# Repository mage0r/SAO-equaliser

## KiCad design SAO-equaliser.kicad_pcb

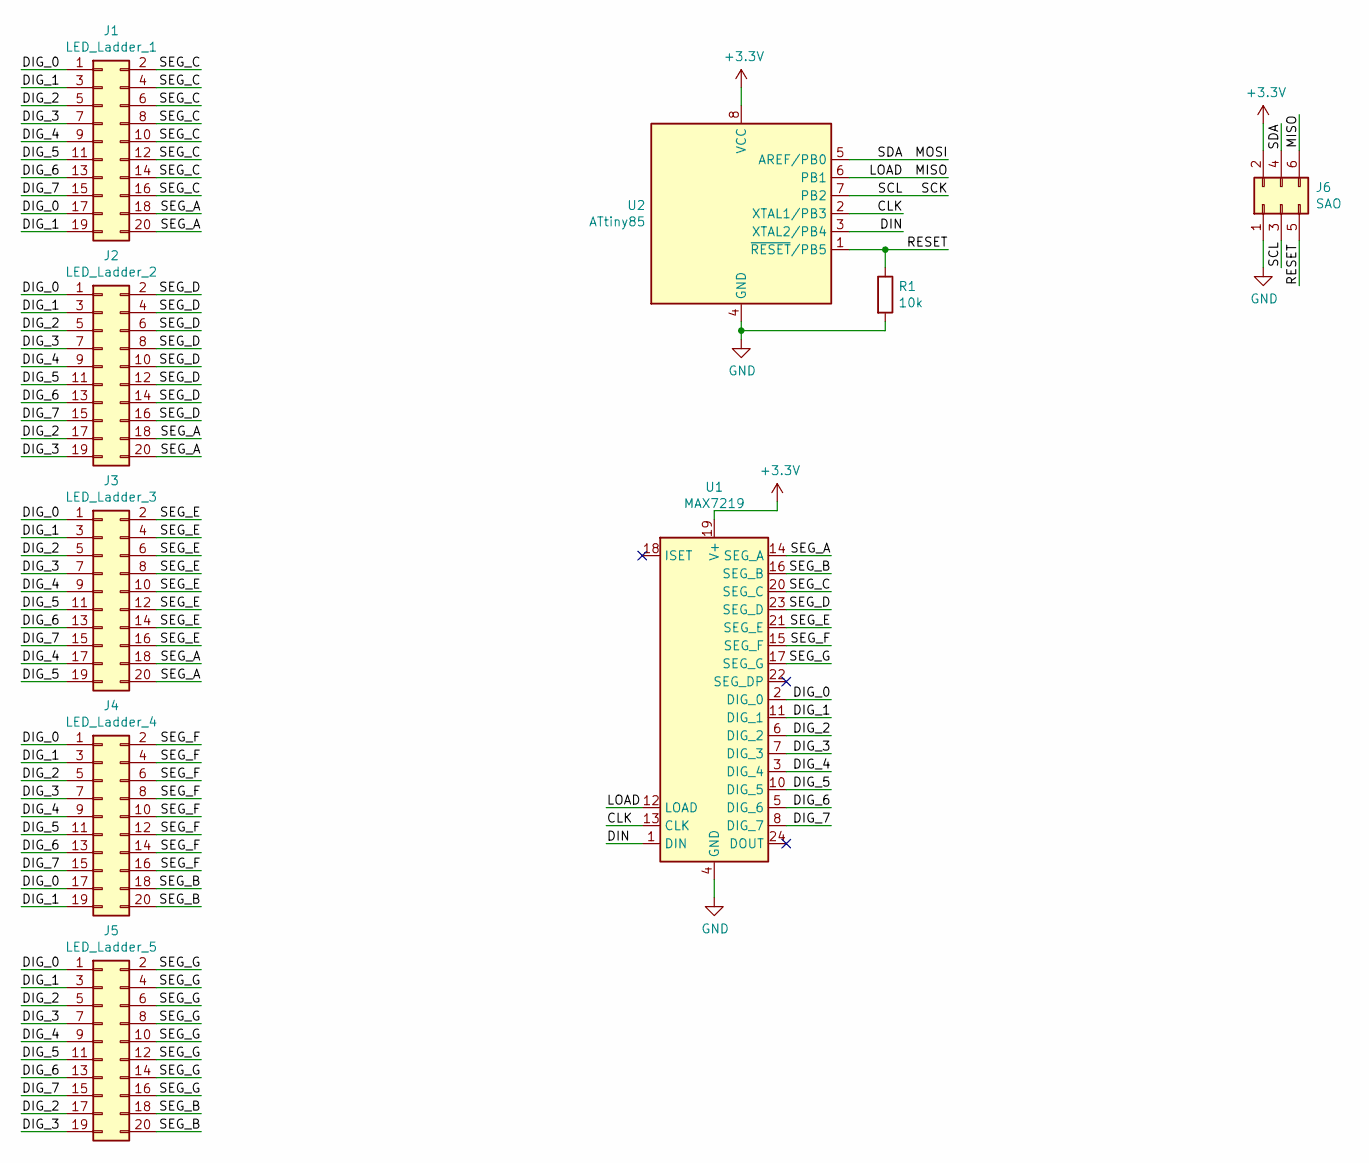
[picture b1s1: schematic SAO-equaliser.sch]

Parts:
J1: LED_Ladder_1; LED_array
J2: LED_Ladder_2; LED_array
J3: LED_Ladder_3; LED_array
J4: LED_Ladder_4; LED_array
J5: LED_Ladder_5; LED_array
J6: SAO; PinHeader_2x03_P2.54mm_Vertical
R1: 10k; R_0805_2012Metric_Pad1.15x1.40mm_HandSolder
U1: MAX7219; SOIC-24W_7.5x15.4mm_P1.27mm
U2: ATtiny85; SOIJ-8_5.3x5.3mm_P1.27mm

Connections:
+3V3: J6.2, U1.19 (V+), U2.8 (VCC)
/CLK: U1.13 (CLK), U2.2 (XTAL1/PB3)
/DIG_0: J1.1, J1.17, J2.1, J3.1, J4.1, J4.17, J5.1, U1.2 (DIG_0)
/DIG_1: J1.3, J1.19, J2.3, J3.3, J4.3, J4.19, J5.3, U1.11 (DIG_1)
/DIG_2: J1.5, J2.5, J2.17, J3.5, J4.5, J5.5, J5.17, U1.6 (DIG_2)
/DIG_3: J1.7, J2.7, J2.19, J3.7, J4.7, J5.7, J5.19, U1.7 (DIG_3)
/DIG_4: J1.9, J2.9, J3.9, J3.17, J4.9, J5.9, U1.3 (DIG_4)
/DIG_5: J1.11, J2.11, J3.11, J3.19, J4.11, J5.11, U1.10 (DIG_5)
/DIG_6: J1.13, J2.13, J3.13, J4.13, J5.13, U1.5 (DIG_6)
/DIG_7: J1.15, J2.15, J3.15, J4.15, J5.15, U1.8 (DIG_7)
/DIN: U1.1 (DIN), U2.3 (XTAL2/PB4)
/LOAD: J6.6, U1.12 (LOAD), U2.6 (PB1)
/MOSI: J6.4, U2.5 (AREF/PB0)
/RESET: J6.5, R1.1, U2.1 (~RESET~/PB5)
/SCK: J6.3, U2.7 (PB2)
/SEG_A: J1.18, J1.20, J2.18, J2.20, J3.18, J3.20, U1.14 (SEG_A)
/SEG_B: J4.18, J4.20, J5.18, J5.20, U1.16 (SEG_B)
/SEG_C: J1.2, J1.4, J1.6, J1.8, J1.10, J1.12, J1.14, J1.16, U1.20 (SEG_C)
/SEG_D: J2.2, J2.4, J2.6, J2.8, J2.10, J2.12, J2.14, J2.16, U1.23 (SEG_D)
/SEG_E: J3.2, J3.4, J3.6, J3.8, J3.10, J3.12, J3.14, J3.16, U1.21 (SEG_E)
/SEG_F: J4.2, J4.4, J4.6, J4.8, J4.10, J4.12, J4.14, J4.16, U1.15 (SEG_F)
/SEG_G: J5.2, J5.4, J5.6, J5.8, J5.10, J5.12, J5.14, J5.16, U1.17 (SEG_G)
GND: J6.1, R1.2, U1.4 (GND), U1.9 (GND), U2.4 (GND)

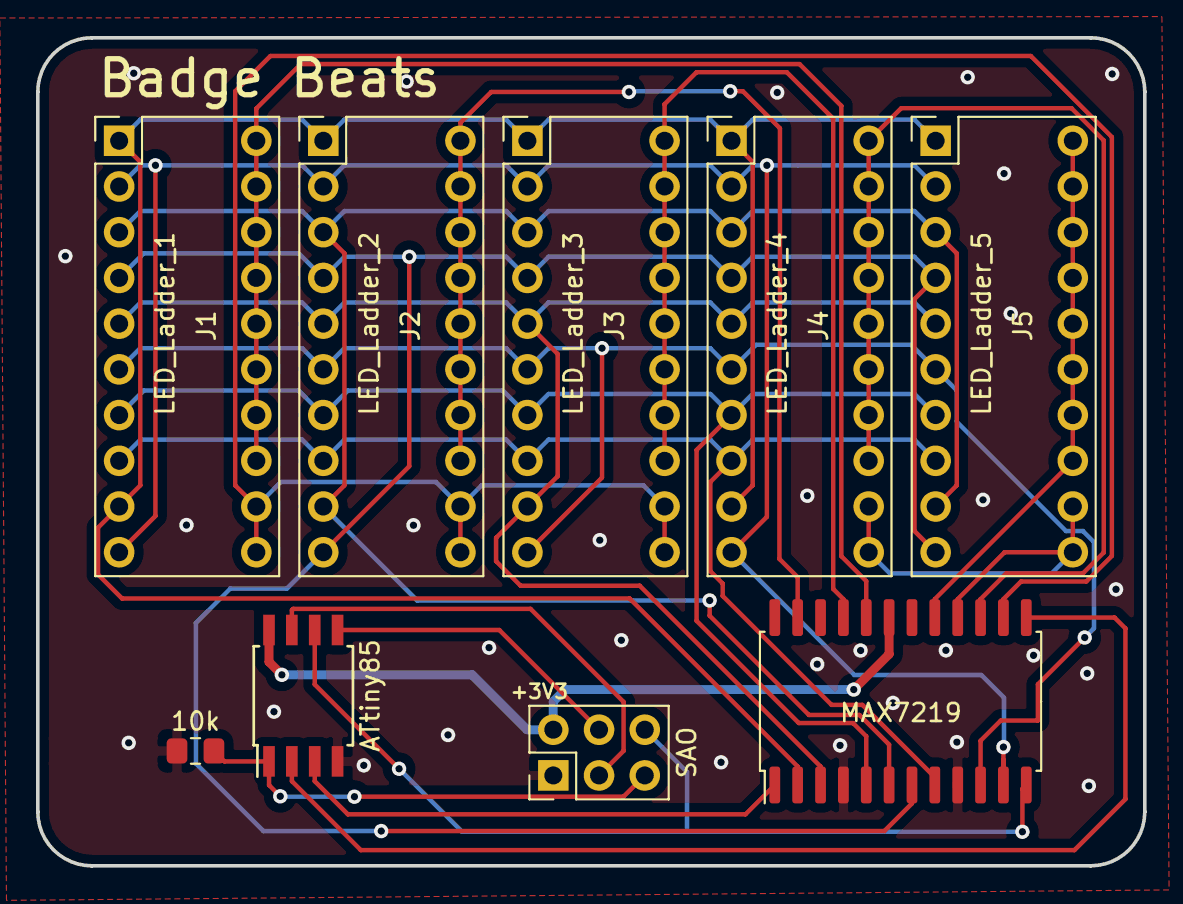
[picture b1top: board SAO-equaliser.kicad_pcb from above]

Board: 2 copper layers, 61.5 x 46.0 mm, 9 parts (0 on the bottom side), 23 nets.

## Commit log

2021-09-30 :neckbeard: Added .gitattributes & .gitignore files
2021-09-30 Initial Publish
    Board is designed.
    but not working.
2021-09-30 Arduino Code examples
    These are horrible. Test purposes only!
